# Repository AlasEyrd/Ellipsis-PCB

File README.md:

# Ellipsis PCB

A PCB for the Ellipsis split keyboard by rutomoda.

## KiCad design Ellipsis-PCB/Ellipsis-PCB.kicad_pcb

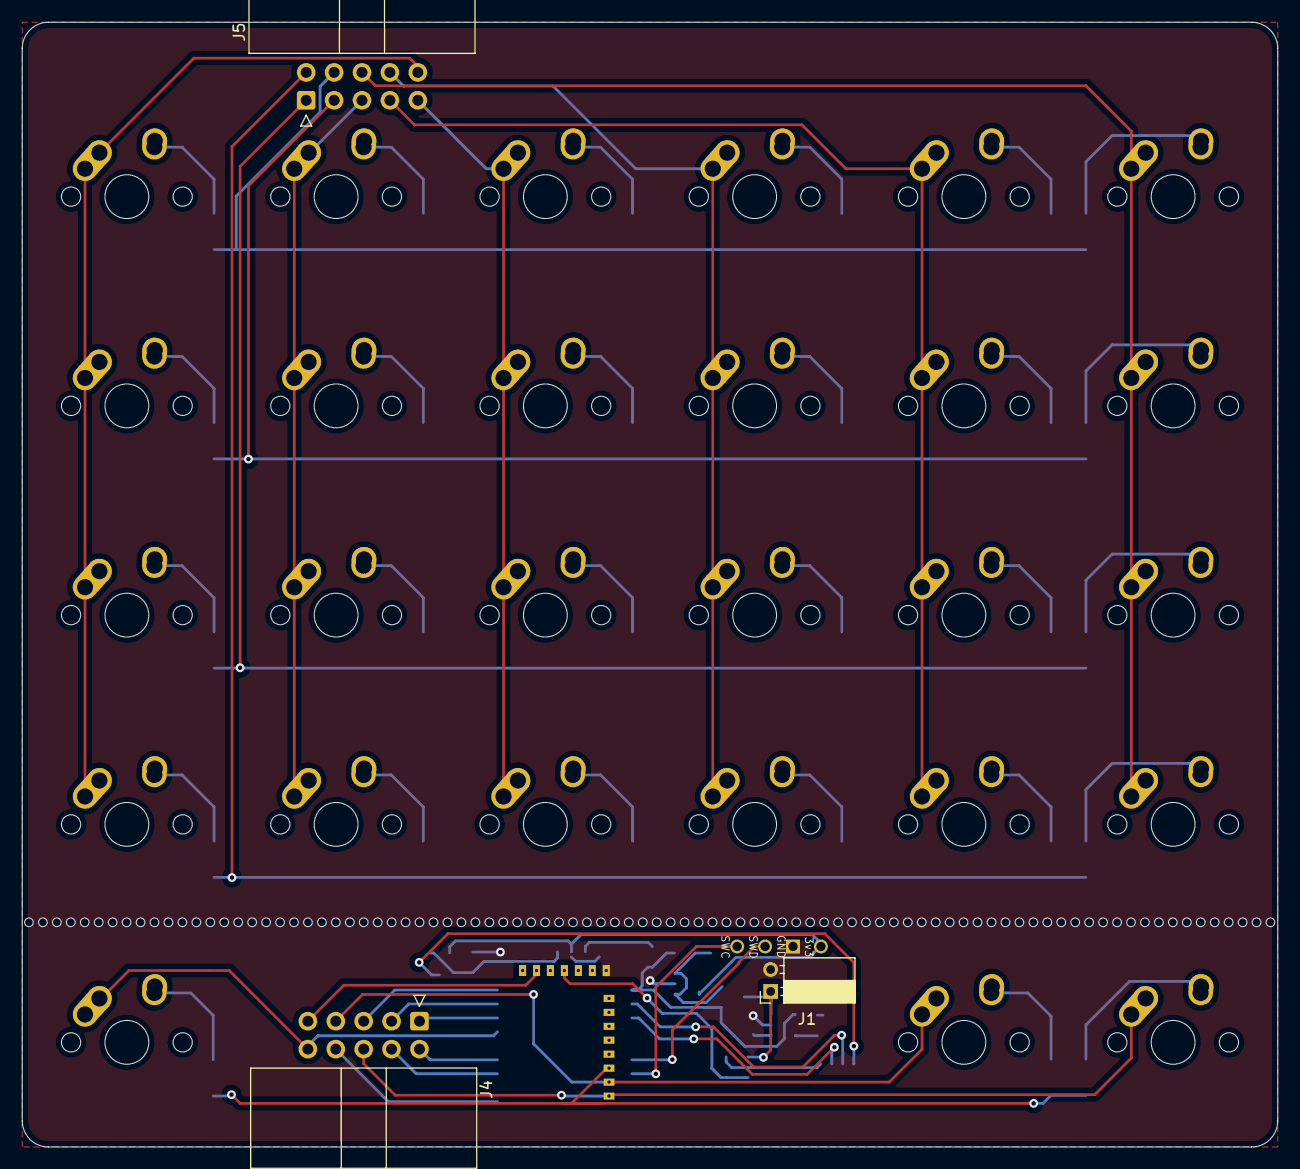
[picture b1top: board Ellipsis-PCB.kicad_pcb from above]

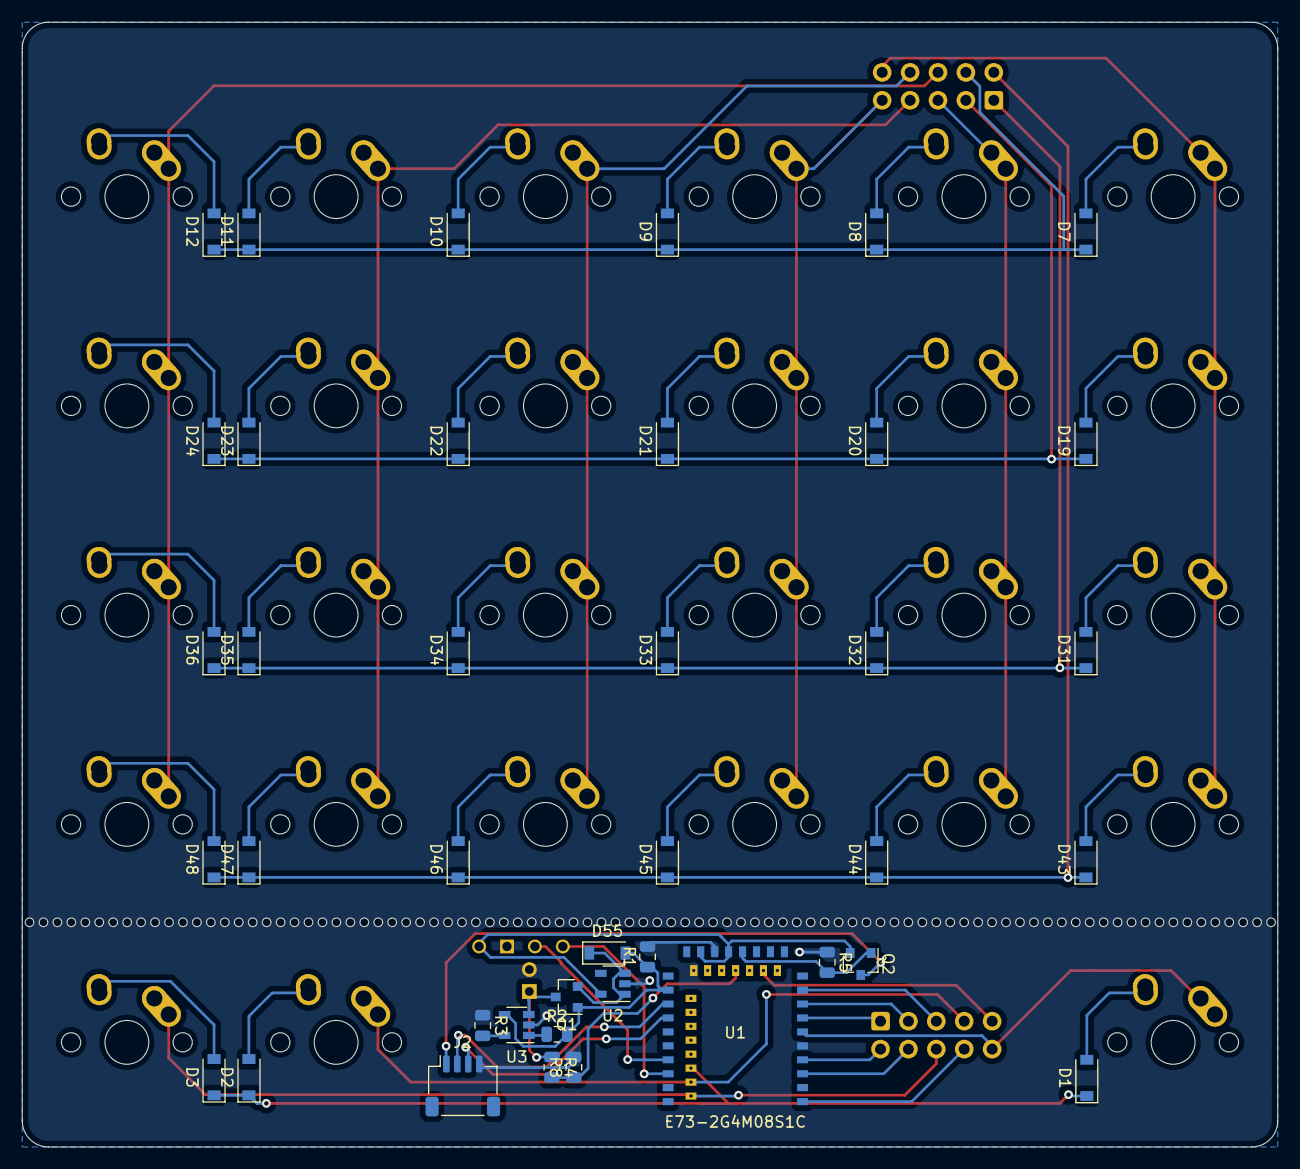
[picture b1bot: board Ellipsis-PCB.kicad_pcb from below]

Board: 2 copper layers, 114.3 x 102.4 mm, 71 parts (41 on the bottom side), 52 nets.

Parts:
D1, D2, D3, D7, D8, D9, D10, D11, D12, D19, D20, D21, D22, D23, D24, D31, D32, D33, D34, D35, D36, D43, D44, D45, D46, D47, D48: D_Small; D_SOD-123-Pretty
D55: 1N5819; D_SOD-123-Pretty
J1: Ex_Bat; PinSocket_1x02_P2.00mm_Horizontal
J2: USB; JST_SH_SM04B-SRSS-TB_1x04-1MP_P1.00mm_Horizontal
J3: SWD; connector_swd
J4, J5: Conn_02x05_Counter_Clockwise; IDC-Header_2x05_P2.54mm_Horizontal
MX1, MX2, MX3, MX7, MX8, MX9, MX10, MX11, MX12, MX19, MX20, MX21, MX22, MX23, MX24, MX31, MX32, MX33, MX34, MX35, MX36, MX43, MX44, MX45, MX46, MX47, MX48: MX-NoLED; MX-1U-NoLED
Q1, Q2: AO3407; SOT-23
R1: 100k; R_0805_2012Metric
R2: 1k; R_0805_2012Metric
R3: RPROG; R_0805_2012Metric
R4: 820K; R_0805_2012Metric
R5, R8: 2M; R_0805_2012Metric
U1: E73-2G4M08S1C-52840
U2: XC6220B331MR-G; SOT-23-5
U3: MCP73831-3-OT; SOT-23-5

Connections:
BATTERY_PIN: R4.2, R8.1, U1.18
COL0: J4.10, J5.10, MX1.1, MX7.1, MX19.1, MX31.1, MX43.1, U1.6
COL1: J4.5, J5.5, MX8.1, MX20.1, MX32.1, MX44.1, U1.9
COL2: J4.9, J5.9, MX9.1, MX21.1, MX33.1, MX45.1, U1.14
COL3: J4.8, J5.8, MX10.1, MX22.1, MX34.1, MX46.1, U1.1
COL4: J4.7, J5.7, MX2.1, MX11.1, MX23.1, MX35.1, MX47.1, U1.40
COL5: J4.6, J5.6, MX3.1, MX12.1, MX24.1, MX36.1, MX48.1, U1.42
D+: J2.3, U1.31
D-: J2.2, U1.29
EXT_VCC: J2.1, Q2.3
GND: J1.2, J2.4, J3.2, R1.2, R3.1, R5.1, R8.2, U1.5, U1.21, U1.24, U2.2, U3.2
unnamed: D1.2, MX1.2
unnamed: D2.2, MX2.2
unnamed: D3.2, MX3.2
unnamed: D7.2, MX7.2
unnamed: D8.2, MX8.2
unnamed: D9.2, MX9.2
unnamed: D10.2, MX10.2
unnamed: D11.2, MX11.2
unnamed: D12.2, MX12.2
unnamed: D19.2, MX19.2
unnamed: D20.2, MX20.2
unnamed: D21.2, MX21.2
unnamed: D22.2, MX22.2
unnamed: D23.2, MX23.2
unnamed: D24.2, MX24.2
unnamed: D31.2, MX31.2
unnamed: D32.2, MX32.2
unnamed: D33.2, MX33.2
unnamed: D34.2, MX34.2
unnamed: D35.2, MX35.2
unnamed: D36.2, MX36.2
unnamed: D43.2, MX43.2
unnamed: D44.2, MX44.2
unnamed: D45.2, MX45.2
unnamed: D46.2, MX46.2
unnamed: D47.2, MX47.2
unnamed: D48.2, MX48.2
unnamed: D55.1, Q1.2, U2.1, U2.3
unnamed: R2.1, U3.1
unnamed: R3.2, U3.5
POWER_PIN: Q2.1, R5.2, U1.17
ROW0: D43.1, D44.1, D45.1, D46.1, D47.1, D48.1, J4.2, J5.2, U1.4
ROW1: D31.1, D32.1, D33.1, D34.1, D35.1, D36.1, J4.1, J5.1, U1.7
ROW2: D19.1, D20.1, D21.1, D22.1, D23.1, D24.1, J4.3, J5.3, U1.8
ROW3: D7.1, D8.1, D9.1, D10.1, D11.1, D12.1, J4.4, J5.4, U1.3
ROW4: D1.1, D2.1, D3.1, U1.38
SWC: J3.4, U1.39
SWD: J3.3, U1.37
VBAT: J1.1, Q1.3, R4.1, U3.3
VBUS: D55.2, Q1.1, R1.1, R2.2, U1.27, U3.4
nRF_VDD: J3.1, Q2.2, U1.19, U1.23, U2.5

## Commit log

2020-11-13 Rev 1 (left only)
2020-11-13 More things
    Added mousebites and the right half
